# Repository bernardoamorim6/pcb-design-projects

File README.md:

# PCB Design Projects

Two PCB design projects completed during my Electronics and Computer
Engineering studies (KU Leuven exchange). Both were taken through
schematic capture, layout, and design-rule checking in Autodesk EAGLE,
with fabrication-ready Gerber files generated as the final output.

**Note:** these were coursework design exercises. Neither board was
physically fabricated or assembled as part of the coursework — the
work here covers design and verification (schematic, layout, DRC,
Gerber export), not hardware build or bring-up.

| Project | Focus | Layers |
|---|---|---|
| [HD-SDI Cable Equalizer](./hd-sdi-cable-equalizer) | RF/high-speed signal design | 4 |
| [PCB Manufacturing Exercise](./pcb-manufacturing-exercise) | Fabrication design-rules & via optimization | 4 |

---

## HD-SDI Cable Equalizer

A 4-layer PCB design for an adaptive cable equalizer circuit, used to
condition HD-SDI (broadcast video) signals. Includes:

- Schematic built around a GS3440 Adaptive Cable Equalizer IC
- Impedance-controlled microstrip trace design: 50Ω traces for SMA
  connectors, 75Ω traces for HD-BNC connectors
- Full 4-layer stackup (top, two inner routing layers, bottom)
- Complete Gerber output set (copper, soldermask, silkscreen,
  solder paste, drill/profile)

 | 

(images generated from gerber files)

## PCB Manufacturing Exercise

A design exercise focused on PCB fabrication constraints rather than
circuit function: working through plated-through-hole size classes
(per Eurocircuits manufacturing classes) and via teardrop optimization
for manufacturability.

 | 

(images generated from gerber files)

---

### Tools

Designed in [Autodesk EAGLE](https://www.autodesk.com/products/eagle/overview)
9.6.2. Files are provided in their native `.sch`/`.brd` format alongside
exported Gerbers.

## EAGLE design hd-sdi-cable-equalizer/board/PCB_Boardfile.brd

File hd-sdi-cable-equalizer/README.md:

# HD-SDI Cable Equalizer — PCB Design

A 4-layer PCB designed in Autodesk EAGLE for an adaptive cable
equalizer circuit, intended to condition HD-SDI (broadcast video)
signals carried over coaxial cable.

**Scope:** this is a design exercise — schematic capture, layout,
impedance calculation, design-rule checking, and Gerber export. The
board was not physically fabricated or assembled.

## Design details

- **Core component:** GS3440 Adaptive Cable Equalizer IC
- **RF interfaces:**
  - SMA end-launch connectors, 50Ω impedance-matched traces
  - HD-BNC connector, 75Ω impedance-matched trace (standard for
    broadcast video/SDI)
- **Stackup:** 4 copper layers (Top, two inner routing layers, Bottom),
  ~1.63mm total board thickness
- **Trace impedance:** calculated using surface microstrip formulas
  (FR4 dielectric, Er = 4.2) to match connector impedance specs

## Files

| Folder | Contents |
|---|---|
| `schematic/` | EAGLE schematic (`.sch`) |
| `board/` | EAGLE board/layout file (`.brd`) |
| `gerbers/` | Fabrication-ready Gerber files (copper, soldermask, silkscreen, solder paste, drill/profile) |
| `BOM.txt` | Bill of materials exported from EAGLE |

## Tools

Autodesk EAGLE 9.6.2.

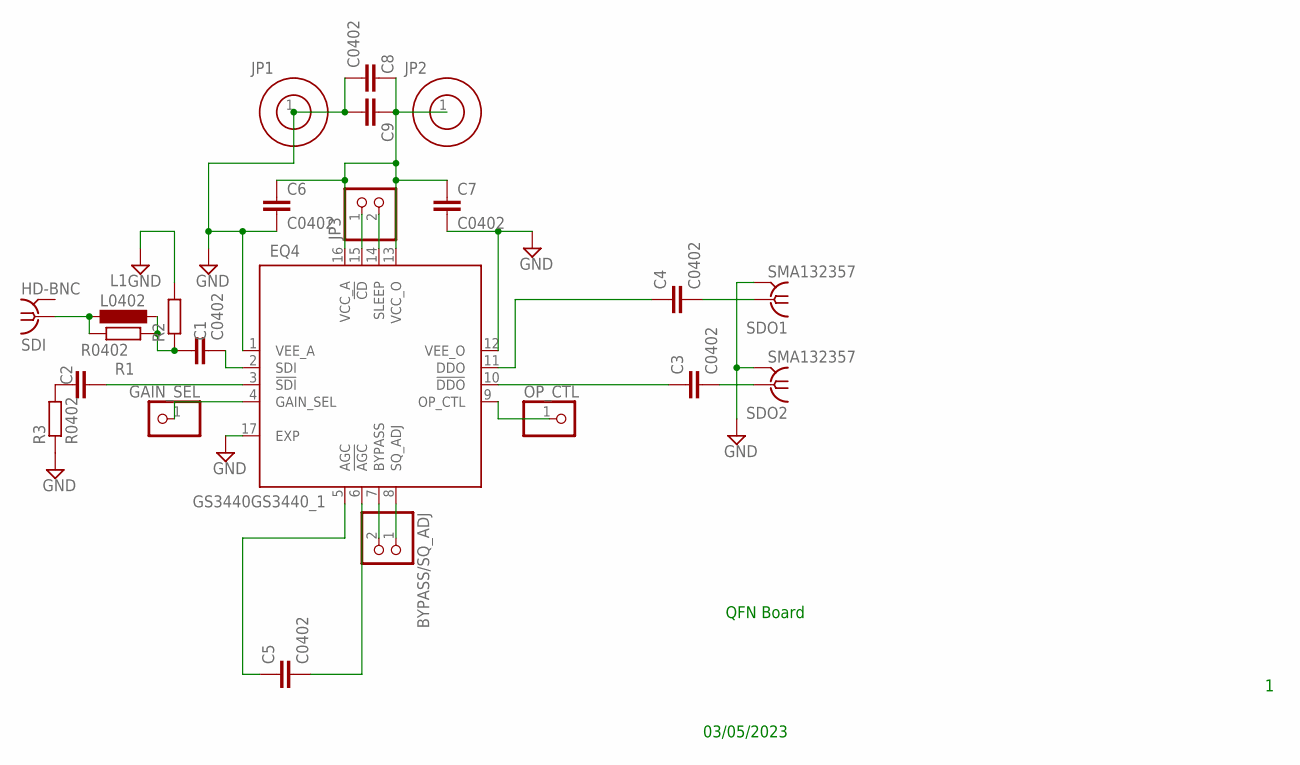
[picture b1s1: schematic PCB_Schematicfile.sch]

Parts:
BYPASS/SQ_ADJ: PINHD-1X2; 1X02
C1, C2, C3, C4, C5, C6, C7, C8: C0402; 0402
C9: C-EUC0805; C0805
EQ4: GS3440GS3440_1; QFN65P400X400X90-17T260N
GAIN_SEL: PINHD-1X1; 1X01
JP1, JP2: 4MMSOCKET; 4MM
JP3: PINHD-1X2; 1X02
L1: L0402; 0402
OP_CTL: PINHD-1X1; 1X01
R1, R2, R3: R0402; 0402
SDI: HD-BNC; 034_1018_12G
SDO1, SDO2: SMA132357; SMA

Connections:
33V: C6.1, C7.1, C8.1, C9.1, EQ4.13 (VCC_O), EQ4.16 (VCC_A), JP2.1
75OHM: C1.2, EQ4.2 (SDI)
GND: C6.2, C7.2, C8.2, C9.2, EQ4.1 (VEE_A), EQ4.12 (VEE_O), EQ4.17 (EXP), JP1.1, R2.2, R3.1, SDO1.G@1 (2), SDO1.G@2 (2), SDO1.G@3 (2), SDO1.G@4 (2), SDO2.G@1 (2), SDO2.G@2 (2), SDO2.G@3 (2), SDO2.G@4 (2)
unnamed: C5.2, EQ4.6 (!AGC)
unnamed: C1.1, L1.2, R1.2, R2.1
unnamed: C3.1, EQ4.10 (!DDO)
unnamed: C2.2, EQ4.3 (!SDI)
unnamed: EQ4.4 (GAIN_SEL), GAIN_SEL.1
unnamed: C2.1, R3.2
unnamed: EQ4.15 (!CD), JP3.1
unnamed: C4.1, EQ4.11 (DDO)
unnamed: C4.2, SDO1.1
unnamed: EQ4.14 (SLEEP), JP3.2
unnamed: C5.1, EQ4.5 (AGC)
unnamed: C3.2, SDO2.1
unnamed: L1.1, R1.1, SDI.P$1 (1)
unnamed: BYPASS/SQ_ADJ.2, EQ4.7 (BYPASS)
unnamed: BYPASS/SQ_ADJ.1, EQ4.8 (SQ_ADJ)
unnamed: EQ4.9 (OP_CTL), OP_CTL.1

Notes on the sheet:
QFN Board
03/05/2023

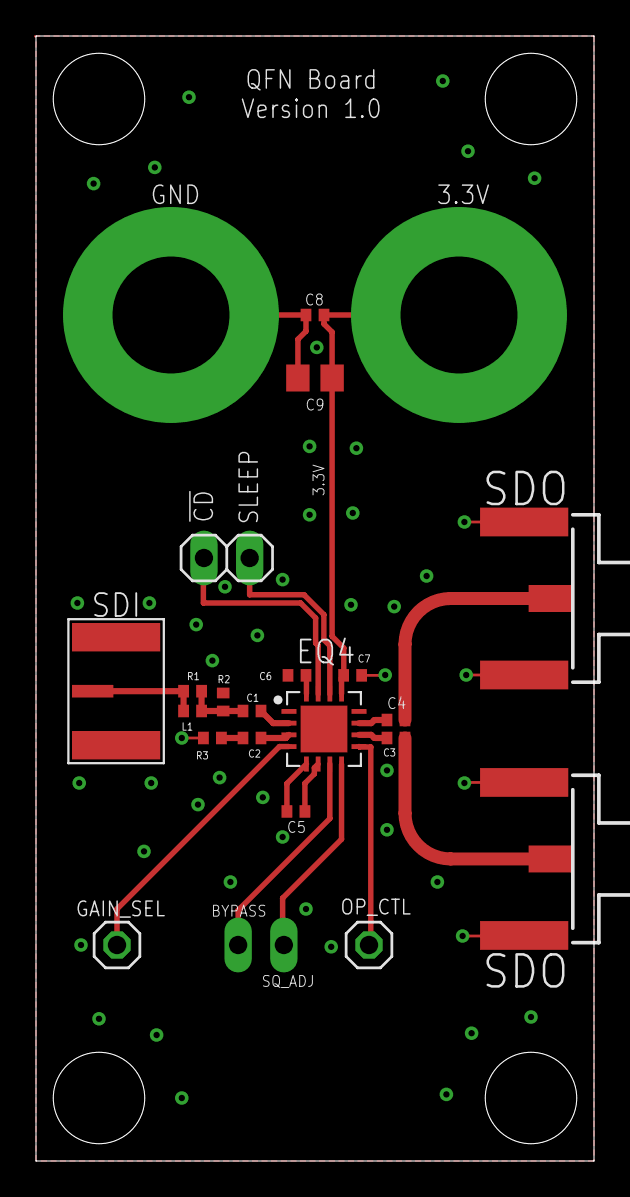
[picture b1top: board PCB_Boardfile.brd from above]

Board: 4 copper layers, 31.0 x 62.5 mm, 23 parts (1 on the bottom side), 19 nets.

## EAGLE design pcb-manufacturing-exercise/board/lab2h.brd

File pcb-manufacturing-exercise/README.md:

# PCB Manufacturing Design-Rule Exercise

A PCB design exercise focused on manufacturing constraints and
fabrication classes, rather than circuit function — working through
how design choices map to real fabrication tolerances.

**Scope:** this is a design exercise — schematic, layout, and Gerber
export. The board was not physically fabricated or assembled.

## What this covers

- Plated-through-hole (PTH) sizing against Eurocircuits fabrication
  classes (e.g. minimum PTH diameter for Class 6C)
- Via teardrop optimization for manufacturability (`via_teardrops1.ulp`,
  applied via `lab2h_AddTearDrops.scr`)
- 4-layer board design and layout in EAGLE

## Files

| Folder | Contents |
|---|---|
| `schematic/` | EAGLE schematic (`.sch`) |
| `board/` | EAGLE board/layout file (`.brd`), teardrop script and ULP |
| `gerbers/` | Fabrication-ready Gerber files |

## Tools

Autodesk EAGLE 9.6.2.

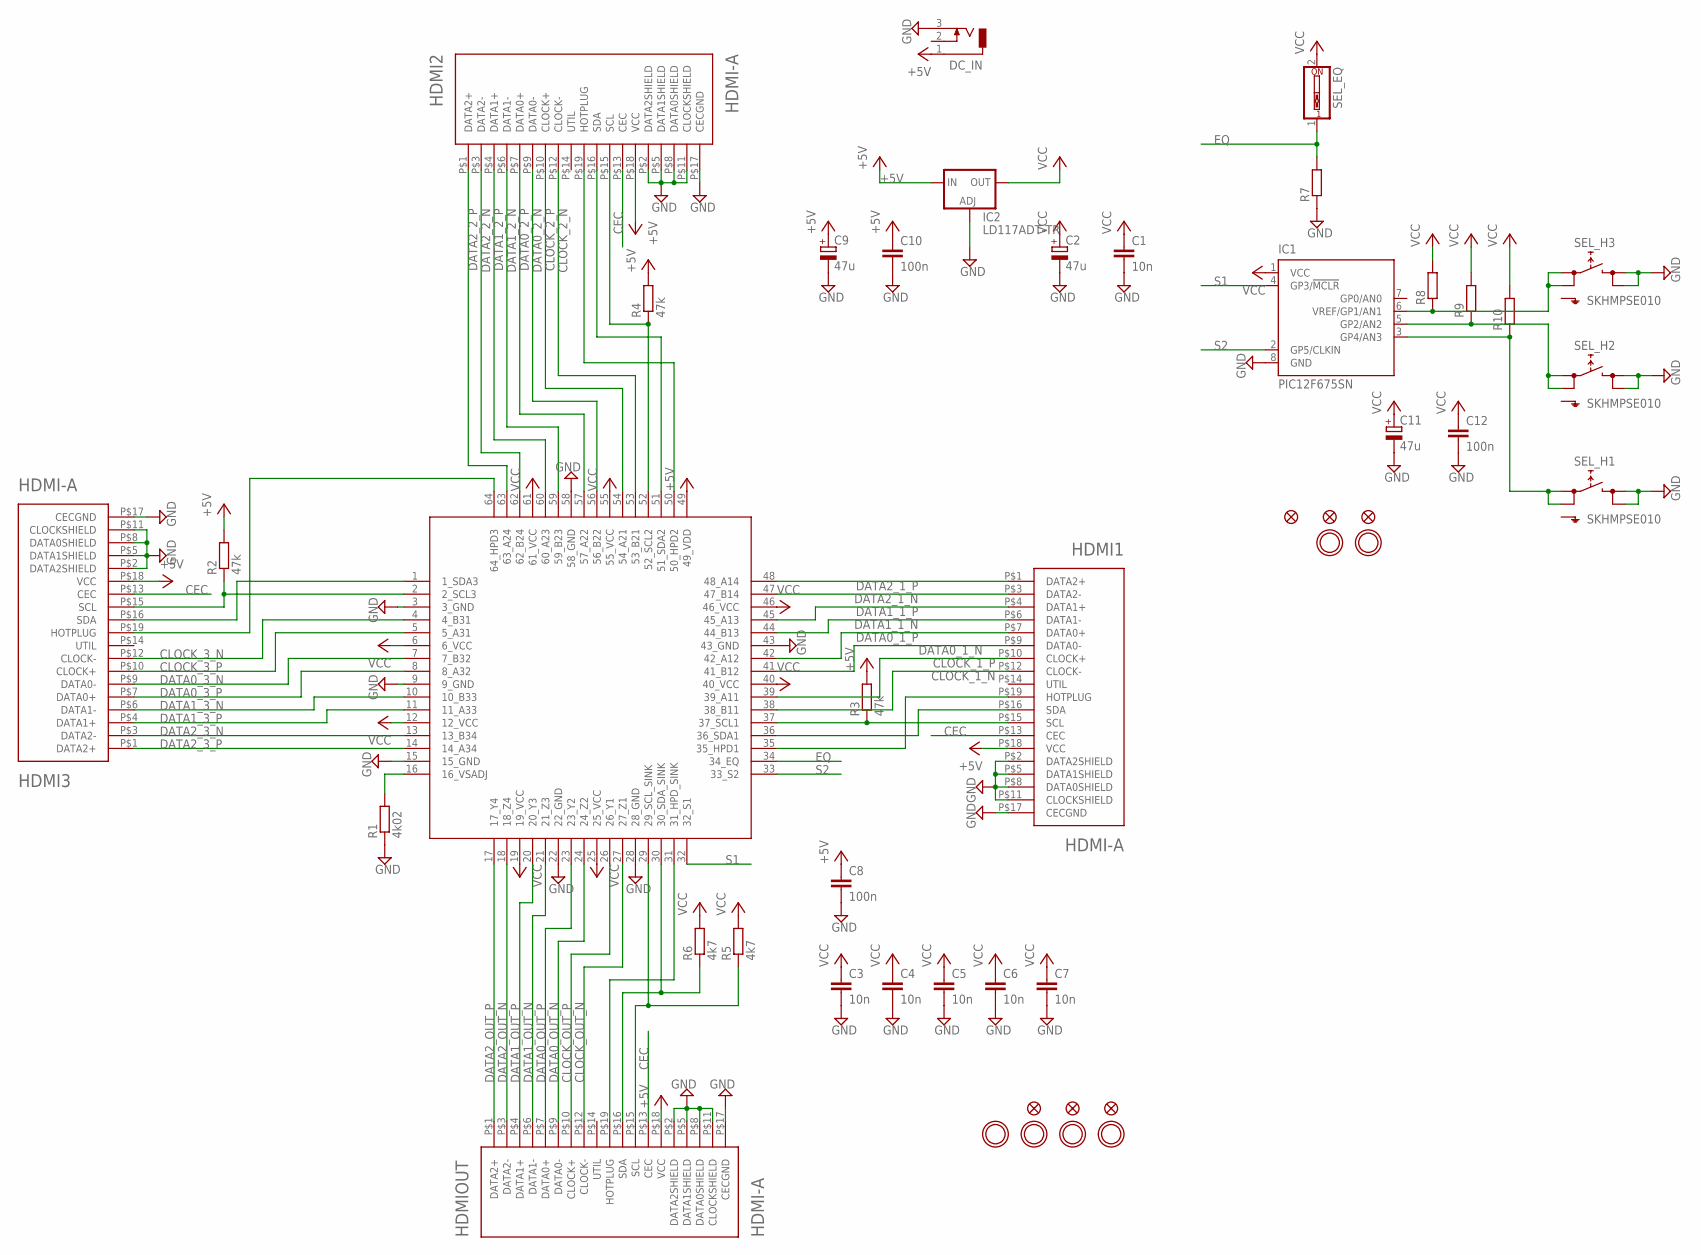
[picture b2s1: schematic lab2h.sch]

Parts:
C1: 10n; C0402
C2, C9, C11: 47u; SMC_A
C3, C4, C5, C6, C7: 10n; 0402
C8: 100n; 0402
C10, C12: 100n; C0402
DC_IN: DCJ0303
FID1, FID2, FID3, FID4, FID5, FID6: FIDUCIAL""; FIDUCIAL_1MM
HDMI1, HDMI2, HDMI3: HDMI-A; HDMI_A
HDMIOUT: HDMI-A; HDMI_A
IC1: PIC12F675SN; SO-08
IC2: LD117ADT-TR; DPACK
R1: 4k02; 0402
R2, R3, R4: 47k; 0402
R5, R6: 4k7; 0402
R7, R8, R9, R10: R-EU_R0805; R0805
SEL_EQ: SW_DIP-1; EDG-01
SEL_H1, SEL_H2, SEL_H3: SKHMPSE010; SKHMPXE010
U1: TMDS351TQFP64; QFP50P1200X1200X120-64
U$1, U$2, U$31, U$32, U$33, U$34: MOUNTINGHOLE3.0; MOUNTINGHOLE_3.0_PLATED

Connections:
+5V: C8.1, C9.+, C10.1, DC_IN.1, HDMI1.P$18 (VCC), HDMI2.P$18 (VCC), HDMI3.P$18 (VCC), HDMIOUT.P$18 (VCC), IC2.3 (IN), R2.2, R3.2, R4.2, U1.49 (49_VDD)
CEC: HDMI1.P$13 (CEC), HDMI2.P$13 (CEC), HDMI3.P$13 (CEC), HDMIOUT.P$13 (CEC)
CLOCK_1_N: HDMI1.P$12 (CLOCK-), U1.38 (38_B11)
CLOCK_1_P: HDMI1.P$10 (CLOCK+), U1.39 (39_A11)
CLOCK_2_N: HDMI2.P$12 (CLOCK-), U1.53 (53_B21)
CLOCK_2_P: HDMI2.P$10 (CLOCK+), U1.54 (54_A21)
CLOCK_3_N: HDMI3.P$12 (CLOCK-), U1.4 (4_B31)
CLOCK_3_P: HDMI3.P$10 (CLOCK+), U1.5 (5_A31)
CLOCK_OUT_N: HDMIOUT.P$12 (CLOCK-), U1.27 (27_Z1)
CLOCK_OUT_P: HDMIOUT.P$10 (CLOCK+), U1.26 (26_Y1)
DATA0_1_N: HDMI1.P$9 (DATA0-), U1.41 (41_B12)
DATA0_1_P: HDMI1.P$7 (DATA0+), U1.42 (42_A12)
DATA0_2_N: HDMI2.P$9 (DATA0-), U1.56 (56_B22)
DATA0_2_P: HDMI2.P$7 (DATA0+), U1.57 (57_A22)
DATA0_3_N: HDMI3.P$9 (DATA0-), U1.7 (7_B32)
DATA0_3_P: HDMI3.P$7 (DATA0+), U1.8 (8_A32)
DATA0_OUT_N: HDMIOUT.P$9 (DATA0-), U1.24 (24_Z2)
DATA0_OUT_P: HDMIOUT.P$7 (DATA0+), U1.23 (23_Y2)
DATA1_1_N: HDMI1.P$6 (DATA1-), U1.44 (44_B13)
DATA1_1_P: HDMI1.P$4 (DATA1+), U1.45 (45_A13)
DATA1_2_N: HDMI2.P$6 (DATA1-), U1.59 (59_B23)
DATA1_2_P: HDMI2.P$4 (DATA1+), U1.60 (60_A23)
DATA1_3_N: HDMI3.P$6 (DATA1-), U1.10 (10_B33)
DATA1_3_P: HDMI3.P$4 (DATA1+), U1.11 (11_A33)
DATA1_OUT_N: HDMIOUT.P$6 (DATA1-), U1.21 (21_Z3)
DATA1_OUT_P: HDMIOUT.P$4 (DATA1+), U1.20 (20_Y3)
DATA2_1_N: HDMI1.P$3 (DATA2-), U1.47 (47_B14)
DATA2_1_P: HDMI1.P$1 (DATA2+), U1.48 (48_A14)
DATA2_2_N: HDMI2.P$3 (DATA2-), U1.62 (62_B24)
DATA2_2_P: HDMI2.P$1 (DATA2+), U1.63 (63_A24)
DATA2_3_N: HDMI3.P$3 (DATA2-), U1.13 (13_B34)
DATA2_3_P: HDMI3.P$1 (DATA2+), U1.14 (14_A34)
DATA2_OUT_N: HDMIOUT.P$3 (DATA2-), U1.18 (18_Z4)
DATA2_OUT_P: HDMIOUT.P$1 (DATA2+), U1.17 (17_Y4)
EQ: R7.2, SEL_EQ.1, U1.34 (34_EQ)
GND: C1.2, C2.-, C3.2, C4.2, C5.2, C6.2, C7.2, C8.2, C9.-, C10.2, C11.-, C12.2, DC_IN.3, HDMI1.P$2 (DATA2SHIELD), HDMI1.P$5 (DATA1SHIELD), HDMI1.P$8 (DATA0SHIELD), HDMI1.P$11 (CLOCKSHIELD), HDMI1.P$17 (CECGND), HDMI2.P$2 (DATA2SHIELD), HDMI2.P$5 (DATA1SHIELD), HDMI2.P$8 (DATA0SHIELD), HDMI2.P$11 (CLOCKSHIELD), HDMI2.P$17 (CECGND), HDMI3.P$2 (DATA2SHIELD), HDMI3.P$5 (DATA1SHIELD), HDMI3.P$8 (DATA0SHIELD), HDMI3.P$11 (CLOCKSHIELD), HDMI3.P$17 (CECGND), HDMIOUT.P$2 (DATA2SHIELD), HDMIOUT.P$5 (DATA1SHIELD), HDMIOUT.P$8 (DATA0SHIELD), HDMIOUT.P$11 (CLOCKSHIELD), HDMIOUT.P$17 (CECGND), IC1.8 (GND), IC2.1 (ADJ), R1.1, R7.1, SEL_H1.3 (2.1), SEL_H1.4 (2.2), SEL_H2.3 (2.1), SEL_H2.4 (2.2), SEL_H3.3 (2.1), SEL_H3.4 (2.2), U1.3 (3_GND), U1.9 (9_GND), U1.15 (15_GND), U1.22 (22_GND), U1.28 (28_GND), U1.43 (43_GND), U1.58 (58_GND)
unnamed: HDMI3.P$19 (HOTPLUG), U1.64 (64_HPD3)
unnamed: HDMI2.P$19 (HOTPLUG), U1.50 (50_HPD2)
unnamed: HDMI1.P$19 (HOTPLUG), U1.35 (35_HPD1)
unnamed: HDMIOUT.P$19 (HOTPLUG), U1.31 (31_HPD_SINK)
unnamed: HDMI3.P$16 (SDA), U1.1 (1_SDA3)
unnamed: HDMI3.P$15 (SCL), R2.1, U1.2 (2_SCL3)
unnamed: HDMI2.P$16 (SDA), U1.51 (51_SDA2)
unnamed: HDMI2.P$15 (SCL), R4.1, U1.52 (52_SCL2)
unnamed: HDMI1.P$15 (SCL), R3.1, U1.37 (37_SCL1)
unnamed: HDMI1.P$16 (SDA), U1.36 (36_SDA1)
unnamed: HDMIOUT.P$16 (SDA), R6.1, U1.30 (30_SDA_SINK)
unnamed: HDMIOUT.P$15 (SCL), R5.1, U1.29 (29_SCL_SINK)
unnamed: R1.2, U1.16 (16_VSADJ)
unnamed: IC1.6 (VREF/GP1/AN1), R8.1, SEL_H3.1 (1.1), SEL_H3.2 (1.2)
unnamed: IC1.5 (GP2/AN2), R9.1, SEL_H2.1 (1.1), SEL_H2.2 (1.2)
unnamed: IC1.3 (GP4/AN3), R10.1, SEL_H1.1 (1.1), SEL_H1.2 (1.2)
S1: IC1.4 (GP3/!MCLR), U1.32 (32_S1)
S2: IC1.2 (GP5/CLKIN), U1.33 (33_S2)
VCC: C1.1, C2.+, C3.1, C4.1, C5.1, C6.1, C7.1, C11.+, C12.1, IC1.1 (VCC), IC2.4 (OUT), R5.2, R6.2, R8.2, R9.2, R10.2, SEL_EQ.2, U1.6 (6_VCC), U1.12 (12_VCC), U1.19 (19_VCC), U1.25 (25_VCC), U1.40 (40_VCC), U1.46 (46_VCC), U1.55 (55_VCC), U1.61 (61_VCC)

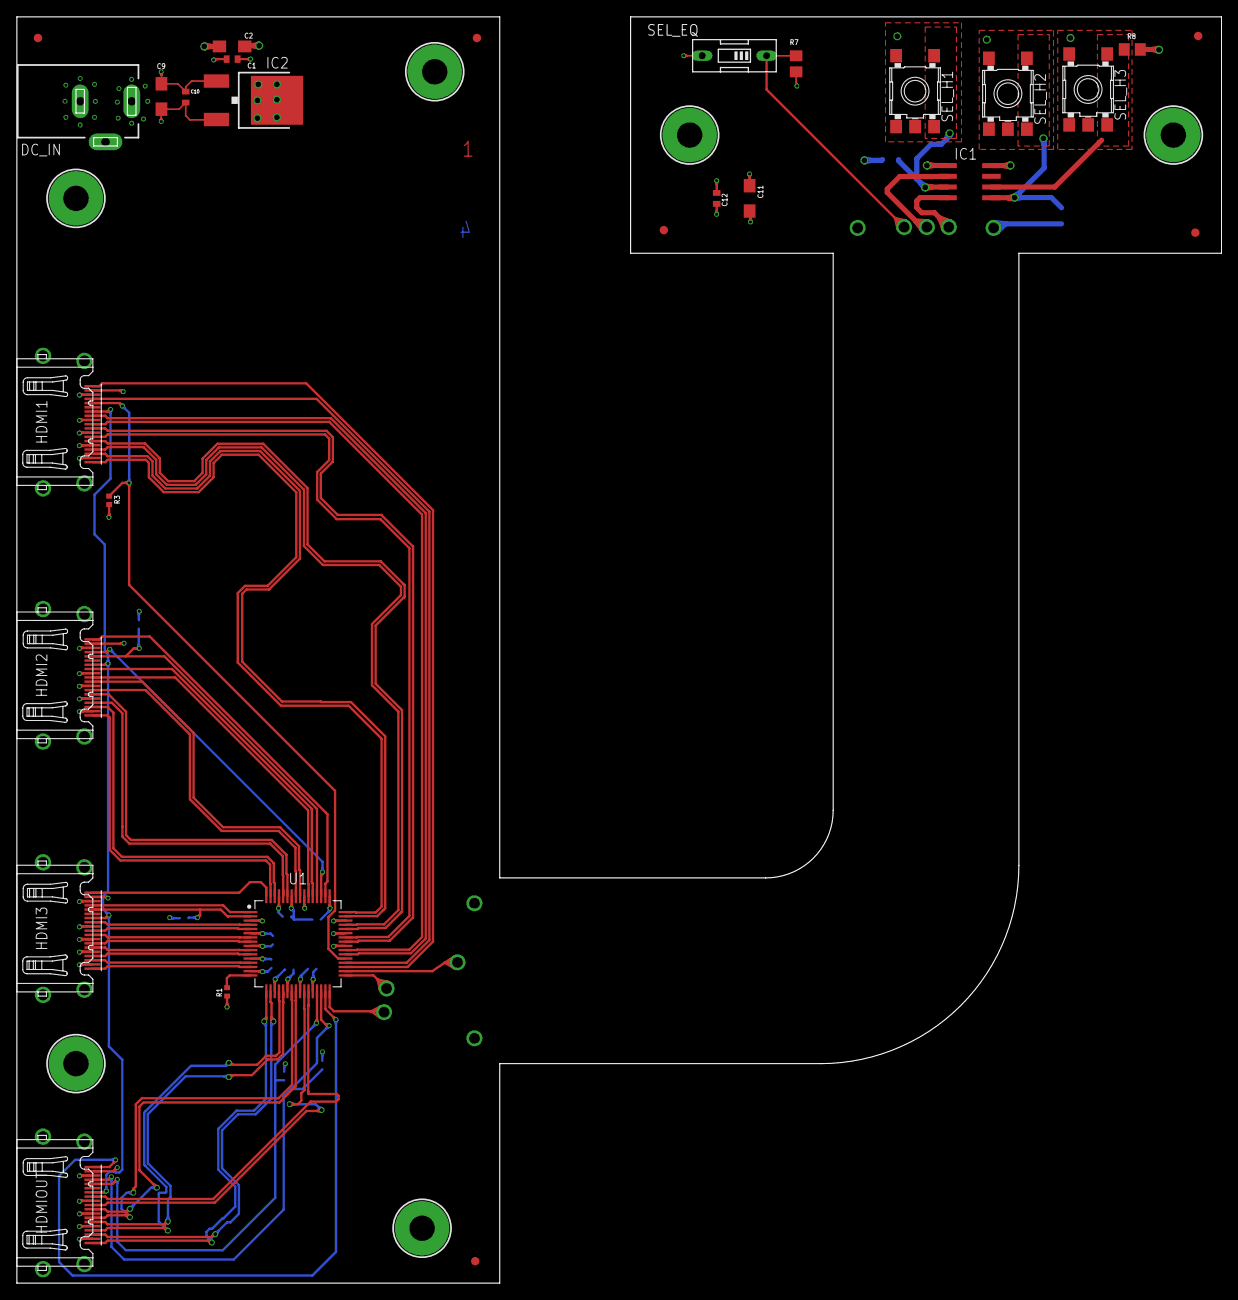
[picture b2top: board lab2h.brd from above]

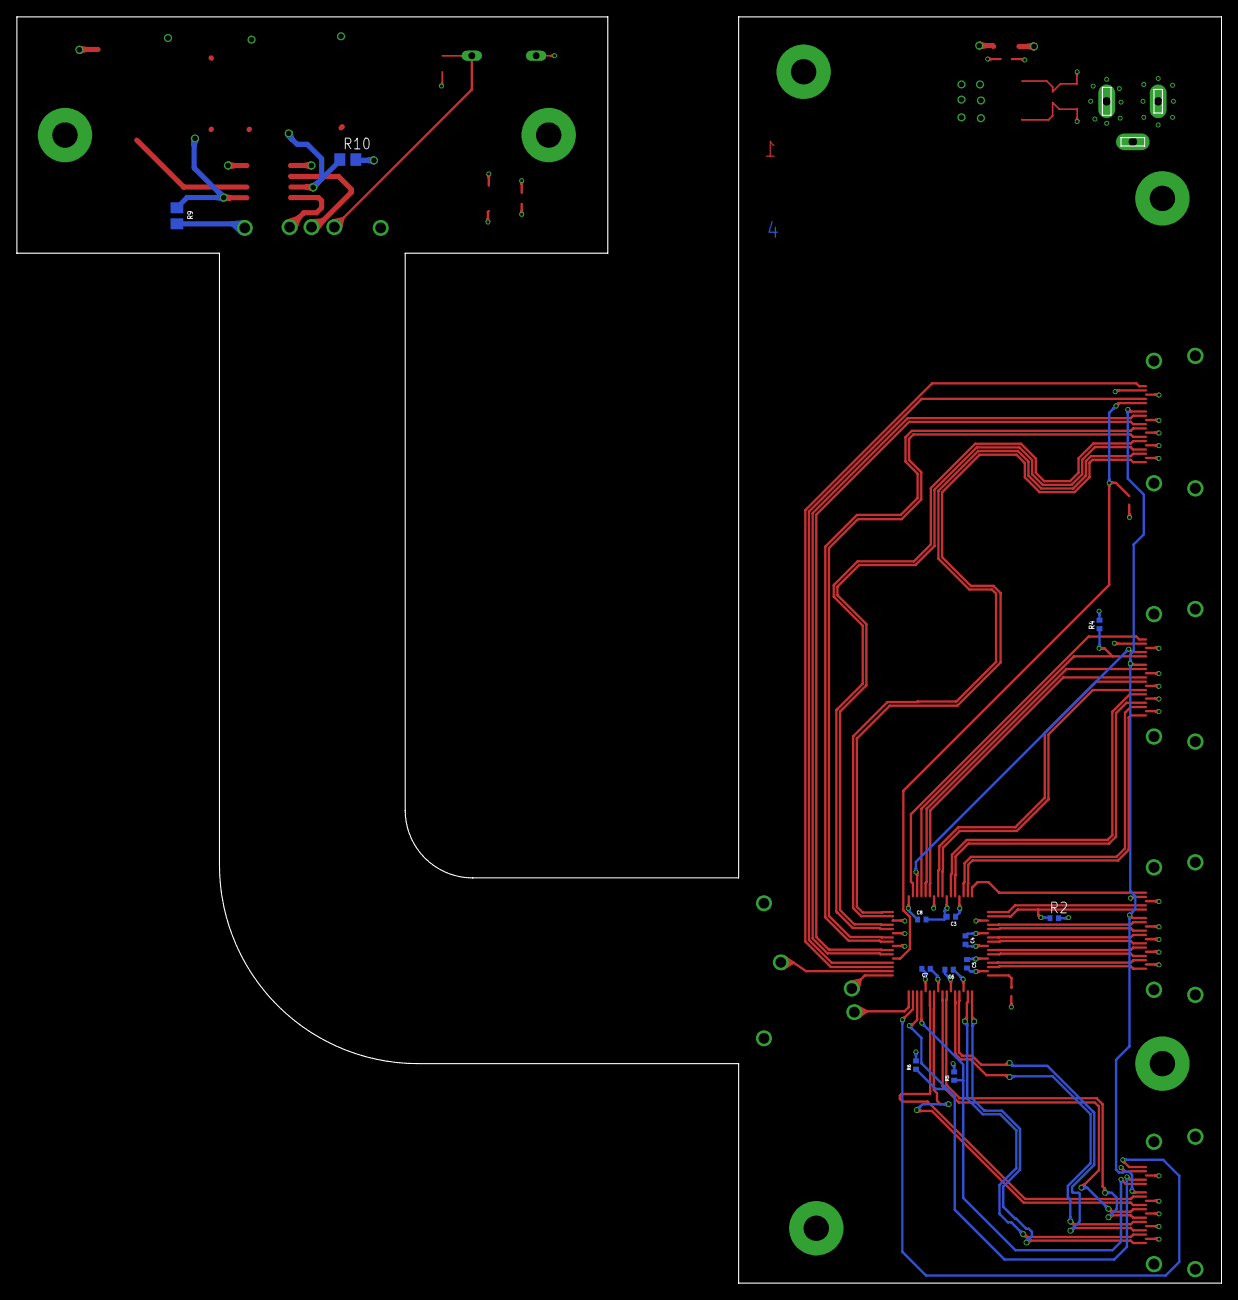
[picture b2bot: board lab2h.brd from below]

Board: 4 copper layers, 142.7 x 150.0 mm, 46 parts (12 on the bottom side), 55 nets.

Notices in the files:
parts and their libraries:
microbuilder: This work is placed in the public domain, and may be freely used for commercial and non-commercial work with the following conditions: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
